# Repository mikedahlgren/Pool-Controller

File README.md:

# Pool Controller

This runs a pool from a [Waveshare ESP32-S3-RELAY-6CH](https://www.waveshare.com/esp32-s3-relay-6ch.htm) and the PoolVeras sensor hat plugged onto its Pico headers.

The Waveshare board talks to the pump, switches the acid pump and the pool light, and reports its own chip temperature. The hat is where the sensors connect: Atlas probe circuits, a 4-20 mA filter-pressure sender, optional pH current loop, DS18B20 temperature sensors, and dry contacts. Home Assistant and the page at `http://pool-controller.local` show the readings. Once an hour the controller can post pH and water temperature to PoolVeras.

## How the hardware is split

| Job | Board |
|-----|--------|
| Pentair IntelliFlo on RS485 | Waveshare, GPIO17 and GPIO18 |
| Acid pump | Waveshare relay CH2, GPIO2 |
| Pool light | Waveshare relay CH6, GPIO46 |
| Waterfall relay | Waveshare relay CH1, GPIO1. Leave it off unless you use it |
| Board temperature | Inside the ESP32-S3. This is the chip, not the pool |
| Atlas pH, ORP, salinity, RTD, or dissolved oxygen | Hat sockets. Any of those boards can go in any pair |
| Filter pressure and other 4-20 mA loops | Hat screw J8. Each loop needs its own 12 V or 24 V supply |
| Air and water temperature | Hat screw J6, DS18B20 sensors. SW3 selects the pull-up. Use 4.7k, handle toward the USB edge |
| Display buttons | SW1 is GPIO7 and SW2 is GPIO6. J17 is the same two switches |
| Dry contacts | Hat screw J7. A bare switch to the GND screw. ON means closed |

CH3, CH4, and CH5 on the Waveshare are free. The hat's 3.3 V rail, through fuse F1, powers the Atlas boards and the 1-Wire sensors. It does not power the 4-20 mA loops.

Screw order on the hat, left to right, is J3 through J8. Probe returns land on PGND next to PRB, not on the board ground screws.

Connector-by-connector wiring is in [esphome/README.md](esphome/README.md). The Waveshare header and onboard GPIO map is in [hardware/WAVESHARE_PINOUT.md](hardware/WAVESHARE_PINOUT.md). Acid dosing is in [esphome/ACID_PH.md](esphome/ACID_PH.md). Filter pressure is in [esphome/FILTER_PRESSURE.md](esphome/FILTER_PRESSURE.md). The board files are in [hardware/sensor-hat](hardware/sensor-hat).

## Install

Use ESPHome 2025.9.0 or newer.

From Home Assistant, paste [`esphome/ha-pool-controller.yaml`](esphome/ha-pool-controller.yaml) into ESPHome Builder. It loads the rest of the firmware from the `PoolverasV1` branch. Copy the keys in [`esphome/secrets.yaml.example`](esphome/secrets.yaml.example) into Home Assistant's `secrets.yaml`, then Install.

From a clone of this repo:

```bash
esphome run esphome/pool-controller.yaml
```

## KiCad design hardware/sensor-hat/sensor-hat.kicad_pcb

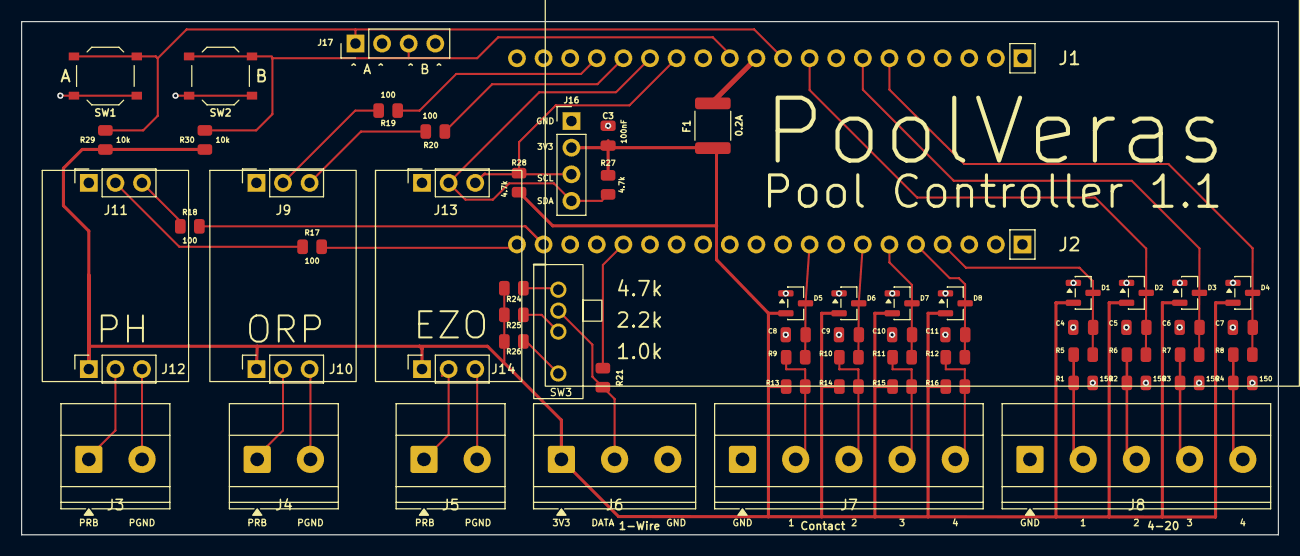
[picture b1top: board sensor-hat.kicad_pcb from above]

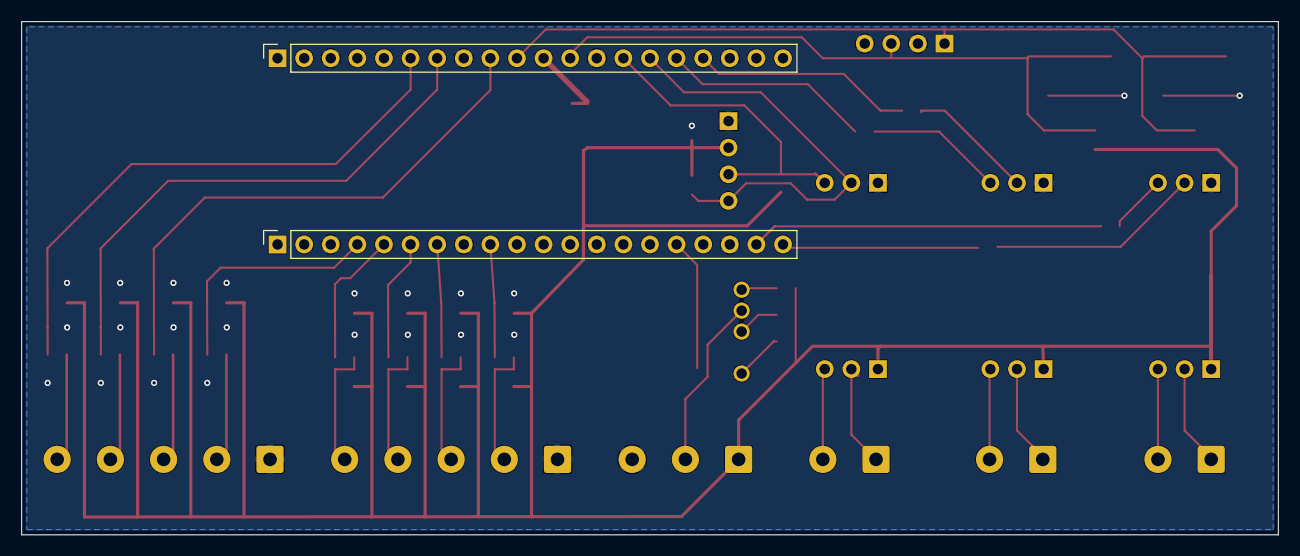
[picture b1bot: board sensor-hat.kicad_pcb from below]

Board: 2 copper layers, 120.0 x 49.0 mm, 69 parts (2 on the bottom side), 42 nets.

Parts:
C3, C4, C5, C6, C7, C8, C9, C10, C11: 100nF; C_0805
D1, D2, D3, D4, D5, D6, D7, D8: BAT54S; SOT-23
DISP1: SSD1309
EZO1: pH; Atlas_EZO
EZO2: ORP; Atlas_EZO
EZO3: EZO; Atlas_EZO
F1: 0.2A; Fuse_1812_4532Metric
J1, J2: 1x20 socket, bottom; PinSocket_1x20_P2.54mm_Vertical
J3: pH probe; TerminalBlock_Phoenix_MKDS-1,5-2-5.08_1x02_P5.08mm_Horizont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
J4: ORP probe; TerminalBlock_Phoenix_MKDS-1,5-2-5.08_1x02_P5.08mm_Horizont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
J5: EZO probe; TerminalBlock_Phoenix_MKDS-1,5-2-5.08_1x02_P5.08mm_Horizont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
J6: 1-Wire; TerminalBlock_Phoenix_MKDS-1,5-3-5.08_1x03_P5.08mm_Horizont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
J7: contacts; TerminalBlock_Phoenix_MKDS-1,5-5-5.08_1x05_P5.08mm_Horizont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
J8: 4-20 mA; TerminalBlock_Phoenix_MKDS-1,5-5-5.08_1x05_P5.08mm_Horizont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
J9, J10, J11, J12, J13, J14: EZO socket, top; PinSocket_1x03_P2.54mm_Vertical
J16: Socket; PinSocket_1x04_P2.54mm_Vertical
J17: external; PinHeader_1x04_P2.54mm_Vertical
R1, R2, R3, R4: 150; R_0805
R5, R6, R7, R8, R9, R10, R11, R12, R26: 1k; R_0805
R13, R14, R15, R16, R29, R30: 10k; R_0805
R17, R18, R19, R20, R21: 100; R_0805
R24, R27, R28: 4.7k; R_0805
R25: 2.2k; R_0805
SW1, SW2: push; SW_Push_1P1T_XKB_TS-1187A
SW3: SK13D07VG5; SW_SK13D07VG5

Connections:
+3V3: F1.1, J1.4, J1.5, J1.11
ADC1: C4.1, D1.3, J2.4, R5.2
ADC2: C5.1, D2.3, J1.9, R6.2
ADC3: C6.1, D3.3, J1.7, R7.2
ADC4: C7.1, D4.3, J1.6, R8.2
BTN1: J1.10, J17.1, R29.2, SW1.1
BTN2: J1.12, J17.3, R30.2, SW2.1
DIN1: C8.1, D5.3, J2.9, R9.2
DIN2: C9.1, D6.3, J2.7, R10.2
DIN3: C10.1, D7.3, J2.6, R11.2
DIN4: C11.1, D8.3, J2.5, R12.2
EOR_RX: J1.17, R19.2
EOR_TX: J1.16, R20.2
EPH_RX: J2.20, R17.2
EPH_TX: J2.19, R18.2
EZO_ORP_RX: J9.3, R20.1
EZO_ORP_TX: J9.2, R19.1
EZO_PGND: J5.2, J14.3
EZO_PH_RX: J11.3, R18.1
EZO_PH_TX: J11.2, R17.1
EZO_PRB: J5.1, J14.2
GND: C3.2, C4.2, C5.2, C6.2, C7.2, C8.2, C9.2, C10.2, C11.2, D1.1, D2.1, D3.1, D4.1, D5.1, D6.1, D7.1, D8.1, J1.3, J1.8, J1.13, J1.18, J2.3, J2.8, J2.13, J2.18, J6.3, J7.1, J8.1, J9.1, J11.1, J13.1, J16.1, J17.2, J17.4, R1.2, R2.2, R3.2, R4.2, SW1.2, SW2.2
IN1: J7.2, R9.1, R13.2
IN2: J7.3, R10.1, R14.2
IN3: J7.4, R11.1, R15.2
IN4: J7.5, R12.1, R16.2
ORP_PGND: J4.2, J10.3
ORP_PRB: J4.1, J10.2
OW: J6.2, R21.1, SW3.3
OWGPIO: J2.16, R21.2
PH_PGND: J3.2, J12.3
PH_PRB: J3.1, J12.2
PU10: R26.2, SW3.4
PU22: R25.2, SW3.2
PU47: R24.2, SW3.1
SCL: J1.14, J13.3, J16.3, R28.2
SDA: J1.15, J13.2, J16.4, R27.2
SIG1: J8.2, R1.1, R5.1
SIG2: J8.3, R2.1, R6.1
SIG3: J8.4, R3.1, R7.1
SIG4: J8.5, R4.1, R8.1
V3OUT: C3.1, D1.2, D2.2, D3.2, D4.2, D5.2, D6.2, D7.2, D8.2, F1.2, J6.1, J10.1, J12.1, J14.1, J16.2, R13.1, R14.1, R15.1, R16.1, R24.1, R25.1, R26.1, R27.1, R28.1, R29.1, R30.1

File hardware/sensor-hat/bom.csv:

Ref,Value,Footprint,Manufacturer,MPN,Package,LCSC
J1,Pin socket 1x20 back side,Connector_PinSocket_2.54mm:PinSocket_1x20_P2.54mm_Vertical,Sullins Connector Solutions,PPPC201LFBN-RC,2.54mm,
J2,Pin socket 1x20 back side,Connector_PinSocket_2.54mm:PinSocket_1x20_P2.54mm_Vertical,Sullins Connector Solutions,PPPC201LFBN-RC,2.54mm,
F1,0.2A,Fuse:Fuse_1812_4532Metric,Bourns,MF-MSMF020-2,1812,
C3,100nF,PCM_JLCPCB:C_0805,Samsung Electro-Mechanics,CL21B104KCFSFNE,0805,
R5,1k,PCM_JLCPCB:R_0805,Yageo,RC0805FR-071KL,0805,
C4,100nF,PCM_JLCPCB:C_0805,Samsung Electro-Mechanics,CL21B104KCFSFNE,0805,
D1,BAT54S,Package_TO_SOT_SMD:SOT-23,onsemi,BAT54SLT1G,SOT-23,
R1,150,PCM_JLCPCB:R_0805,Yageo,RC0805FR-07150RL,0805,
R6,1k,PCM_JLCPCB:R_0805,Yageo,RC0805FR-071KL,0805,
C5,100nF,PCM_JLCPCB:C_0805,Samsung Electro-Mechanics,CL21B104KCFSFNE,0805,
D2,BAT54S,Package_TO_SOT_SMD:SOT-23,onsemi,BAT54SLT1G,SOT-23,
R2,150,PCM_JLCPCB:R_0805,Yageo,RC0805FR-07150RL,0805,
R7,1k,PCM_JLCPCB:R_0805,Yageo,RC0805FR-071KL,0805,
C6,100nF,PCM_JLCPCB:C_0805,Samsung Electro-Mechanics,CL21B104KCFSFNE,0805,
D3,BAT54S,Package_TO_SOT_SMD:SOT-23,onsemi,BAT54SLT1G,SOT-23,
R3,150,PCM_JLCPCB:R_0805,Yageo,RC0805FR-07150RL,0805,
R8,1k,PCM_JLCPCB:R_0805,Yageo,RC0805FR-071KL,0805,
C7,100nF,PCM_JLCPCB:C_0805,Samsung Electro-Mechanics,CL21B104KCFSFNE,0805,
D4,BAT54S,Package_TO_SOT_SMD:SOT-23,onsemi,BAT54SLT1G,SOT-23,
R4,150,PCM_JLCPCB:R_0805,Yageo,RC0805FR-07150RL,0805,
J8,4-20 mA,"TerminalBlock_Phoenix:TerminalBlock_Phoenix_MKDS-1,5_5-5.08_1x05_P5.08mm_Horizontal",Phoenix Contact,1715750,5.08mm,
R9,1k,PCM_JLCPCB:R_0805,Yageo,RC0805FR-071KL,0805,
C8,100nF,PCM_JLCPCB:C_0805,Samsung Electro-Mechanics,CL21B104KCFSFNE,0805,
D5,BAT54S,Package_TO_SOT_SMD:SOT-23,onsemi,BAT54SLT1G,SOT-23,
R13,10k,PCM_JLCPCB:R_0805,Yageo,RC0805FR-0710KL,0805,
R10,1k,PCM_JLCPCB:R_0805,Yageo,RC0805FR-071KL,0805,
C9,100nF,PCM_JLCPCB:C_0805,Samsung Electro-Mechanics,CL21B104KCFSFNE,0805,
D6,BAT54S,Package_TO_SOT_SMD:SOT-23,onsemi,BAT54SLT1G,SOT-23,
R14,10k,PCM_JLCPCB:R_0805,Yageo,RC0805FR-0710KL,0805,
R11,1k,PCM_JLCPCB:R_0805,Yageo,RC0805FR-071KL,0805,
C10,100nF,PCM_JLCPCB:C_0805,Samsung Electro-Mechanics,CL21B104KCFSFNE,0805,
D7,BAT54S,Package_TO_SOT_SMD:SOT-23,onsemi,BAT54SLT1G,SOT-23,
R15,10k,PCM_JLCPCB:R_0805,Yageo,RC0805FR-0710KL,0805,
R12,1k,PCM_JLCPCB:R_0805,Yageo,RC0805FR-071KL,0805,
C11,100nF,PCM_JLCPCB:C_0805,Samsung Electro-Mechanics,CL21B104KCFSFNE,0805,
D8,BAT54S,Package_TO_SOT_SMD:SOT-23,onsemi,BAT54SLT1G,SOT-23,
R16,10k,PCM_JLCPCB:R_0805,Yageo,RC0805FR-0710KL,0805,
J7,Contacts,"TerminalBlock_Phoenix:TerminalBlock_Phoenix_MKDS-1,5_5-5.08_1x05_P5.08mm_Horizontal",Phoenix Contact,1715750,5.08mm,
R21,100,PCM_JLCPCB:R_0805,Yageo,RC0805FR-07100RL,0805,
J6,1-Wire,"TerminalBlock_Phoenix:TerminalBlock_Phoenix_MKDS-1,5_3-5.08_1x03_P5.08mm_Horizontal",Phoenix Contact,1715734,5.08mm,
SW3,SK13D07VG5,SensorHat:SW_SK13D07VG5,SHOU HAN,SK13D07VG5,SP3T,C393948
R24,4.7k,PCM_JLCPCB:R_0805,Yageo,RC0805FR-074K7L,0805,
R25,2.2k,PCM_JLCPCB:R_0805,Yageo,RC0805FR-072K2L,0805,
R26,1k,PCM_JLCPCB:R_0805,Yageo,RC0805FR-071KL,0805,
R17,100,PCM_JLCPCB:R_0805,Yageo,RC0805FR-07100RL,0805,
R18,100,PCM_JLCPCB:R_0805,Yageo,RC0805FR-07100RL,0805,
J11,data socket,Connector_PinSocket_2.54mm:PinSocket_1x03_P2.54mm_Vertical,Sullins Connector Solutions,PPPC031LFBN-RC,2.54mm,
J12,probe socket,Connector_PinSocket_2.54mm:PinSocket_1x03_P2.54mm_Vertical,Sullins Connector Solutions,PPPC031LFBN-RC,2.54mm,
J3,EZO pH probe,"TerminalBlock_Phoenix:TerminalBlock_Phoenix_MKDS-1,5_2-5.08_1x02_P5.08mm_Horizontal",Phoenix Contact,1715721,5.08mm,
R19,100,PCM_JLCPCB:R_0805,Yageo,RC0805FR-07100RL,0805,
R20,100,PCM_JLCPCB:R_0805,Yageo,RC0805FR-07100RL,0805,
J9,data socket,Connector_PinSocket_2.54mm:PinSocket_1x03_P2.54mm_Vertical,Sullins Connector Solutions,PPPC031LFBN-RC,2.54mm,
J10,probe socket,Connector_PinSocket_2.54mm:PinSocket_1x03_P2.54mm_Vertical,Sullins Connector Solutions,PPPC031LFBN-RC,2.54mm,
J4,EZO ORP probe,"TerminalBlock_Phoenix:TerminalBlock_Phoenix_MKDS-1,5_2-5.08_1x02_P5.08mm_Horizontal",Phoenix Contact,1715721,5.08mm,
R28,4.7k,PCM_JLCPCB:R_0805,Yageo,RC0805FR-074K7L,0805,
R27,4.7k,PCM_JLCPCB:R_0805,Yageo,RC0805FR-074K7L,0805,
J16,I2C,Connector_PinSocket_2.54mm:PinSocket_1x04_P2.54mm_Vertical,Sullins Connector Solutions,PPPC041LFBN-RC,2.54mm,
J13,data socket,Connector_PinSocket_2.54mm:PinSocket_1x03_P2.54mm_Vertical,Sullins Connector Solutions,PPPC031LFBN-RC,2.54mm,
J14,probe socket,Connector_PinSocket_2.54mm:PinSocket_1x03_P2.54mm_Vertical,Sullins Connector Solutions,PPPC031LFBN-RC,2.54mm,
J5,EZO I2C probe,"TerminalBlock_Phoenix:TerminalBlock_Phoenix_MKDS-1,5_2-5.08_1x02_P5.08mm_Horizontal",Phoenix Contact,1715721,5.08mm,
R29,10k,PCM_JLCPCB:R_0805,Yageo,RC0805FR-0710KL,0805,
SW1,TS-1187A,Button_Switch_SMD:SW_Push_1P1T_XKB_TS-1187A,XKB Connection,TS-1187A-B-A-B,5.1x5.1mm,C318884
R30,10k,PCM_JLCPCB:R_0805,Yageo,RC0805FR-0710KL,0805,
SW2,TS-1187A,Button_Switch_SMD:SW_Push_1P1T_XKB_TS-1187A,XKB Connection,TS-1187A-B-A-B,5.1x5.1mm,C318884
J17,external,Connector_PinHeader_2.54mm:PinHeader_1x04_P2.54mm_Vertical,Amphenol,68001-404HLF,2.54mm,

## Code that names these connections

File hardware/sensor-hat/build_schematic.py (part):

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            self.raw_syms[lib_id] = rename_symbol(block, lib_id)
        v3 = self.raw_syms["power:+3V3"].replace("+3V3", "V3OUT")
        self.raw_syms["power:V3OUT"] = v3
        self.pins["power:V3OUT"] = dict(self.pins["power:+3V3"])

    def clone_symbol(self, src, lib_id, pin_names, pin_at=None):
        sym_name = lib_id.split(":", 1)[1]
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            ("ADC4  GPIO10", "ADC4"),
        ],
        [
            ("DIN1  GPIO47", "DIN1"),
            ("DIN2  GPIO16", "DIN2"),
            ("DIN3  GPIO15", "DIN3"),
            ("DIN4  GPIO14", "DIN4"),
        ],
        [("1-Wire  GPIO37", "OWGPIO")],
        [("SDA  GPIO4", "SDA"), ("SCL  GPIO5", "SCL")],
        [("pH RX  GPIO12", "EPH_RX"), ("pH TX  GPIO11", "EPH_TX")],
        [("ORP RX  GPIO39", "EOR_RX"), ("ORP TX  GPIO40", "EOR_TX")],
        [("GND", "GND")],
        [("BTN1  GPIO7", "BTN1"), ("BTN2  GPIO6", "BTN2")],
    ]
    right = []
    dy = 0.0
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    def clamp_at(ref, x, y):
        pins = sch.place(
            "Diode:BAT54S", ref, "BAT54S", x, y - 5.08, FP_SOT,
            extra={"LCSC": LCSC["BAT54S"], "Description": "pin 1 GND, pin 2 V3OUT, pin 3 signal"},
        )
        pwr_off(pins["1"], "GND", 0, -5.08)
        pwr_off(pins["2"], "V3OUT", 0, -5.08)
        return pins

    def straight(src, dst):
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        sch.label(f"IN{n}", series["1"][0] + 2.54, y)
        in_rows[n] = pull["1"]

    in_pins = [("GND", -12.7)] + [(f"IN{n}", key_dy[key] - key_dy["DIN1"]) for key, n in contact_rows]
    sch.add_box("sensor-hat:Contact", "Contacts", (), in_pins, width=27.94)
    j8 = sch.place(
        "sensor-hat:Contact", "J7", "Contacts", 400 + 27.94, xy("DIN1")[1], FP_MC.format(n=5),
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
    # 1-Wire. SW3 is on-on-on, so one pull-up is always connected.
    # Pin 3 is the common, on the data net. J6 is the screw terminal.
    y_ow = xy("OWGPIO")[1]
    sch.text(
        "1-Wire. SW3 selects the pull-up. Pin 3 is the data line. Pin 1 is 4.7k, pin 2 is 2.2k, and pin 4 is 1k. The handle toward the USB edge is 4.7k.",
        130, y_ow - 8, 1.2,
    )
    r21 = resistor("R21", "100", 160, y_ow)
    straight(pin["OWGPIO"], r21["2"])
    sch.label("OW", r21["1"][0] + 5.08, y_ow)
    sch.add_box(
        "sensor-hat:OW", "1-Wire", (),
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    )
    j17 = sch.place(
        "Connector_Generic:Conn_01x04", "J17", "external",
        snap(pin["BTN2"][0] + 70), snap(pin["BTN1"][1]),
        "Connector_PinHeader_2.54mm:PinHeader_1x04_P2.54mm_Vertical",
        extra={"Description": "Pin 1 SW1, pin 2 GND, pin 3 SW2, pin 4 GND."},
    )
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
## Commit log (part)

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2026-02-04 Update of the UI to make it more versatile and user friendly
2026-02-09 Created Rust and Zig version added -time option
2026-02-10 added new --ts and --js argumants for generating web dashboards from the native API
